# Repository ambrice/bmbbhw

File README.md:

# Big Mouth Billy Bass Master Control Program

This is the hardware design for the Big Mouth Billy Bass controller.  The current
software (zephyr version) runs on a group of 6 adafruit boards with a lot of
wires running between them.  So this is my first hardware design attempt, to use
the adafruit boards as a reference and compile them into one board.

The adafruit schematics are available under EAGLE which is a dead-end program, so
using KiCad 8 to design the board.  Started with brand-new KiCad 9, but it was
suggested that KiCad 8 would be more stable and have less potential issues with
manufacturing, Osh Park for example accepts KiCad 8 board files directly but not
KiCad 9 yet.

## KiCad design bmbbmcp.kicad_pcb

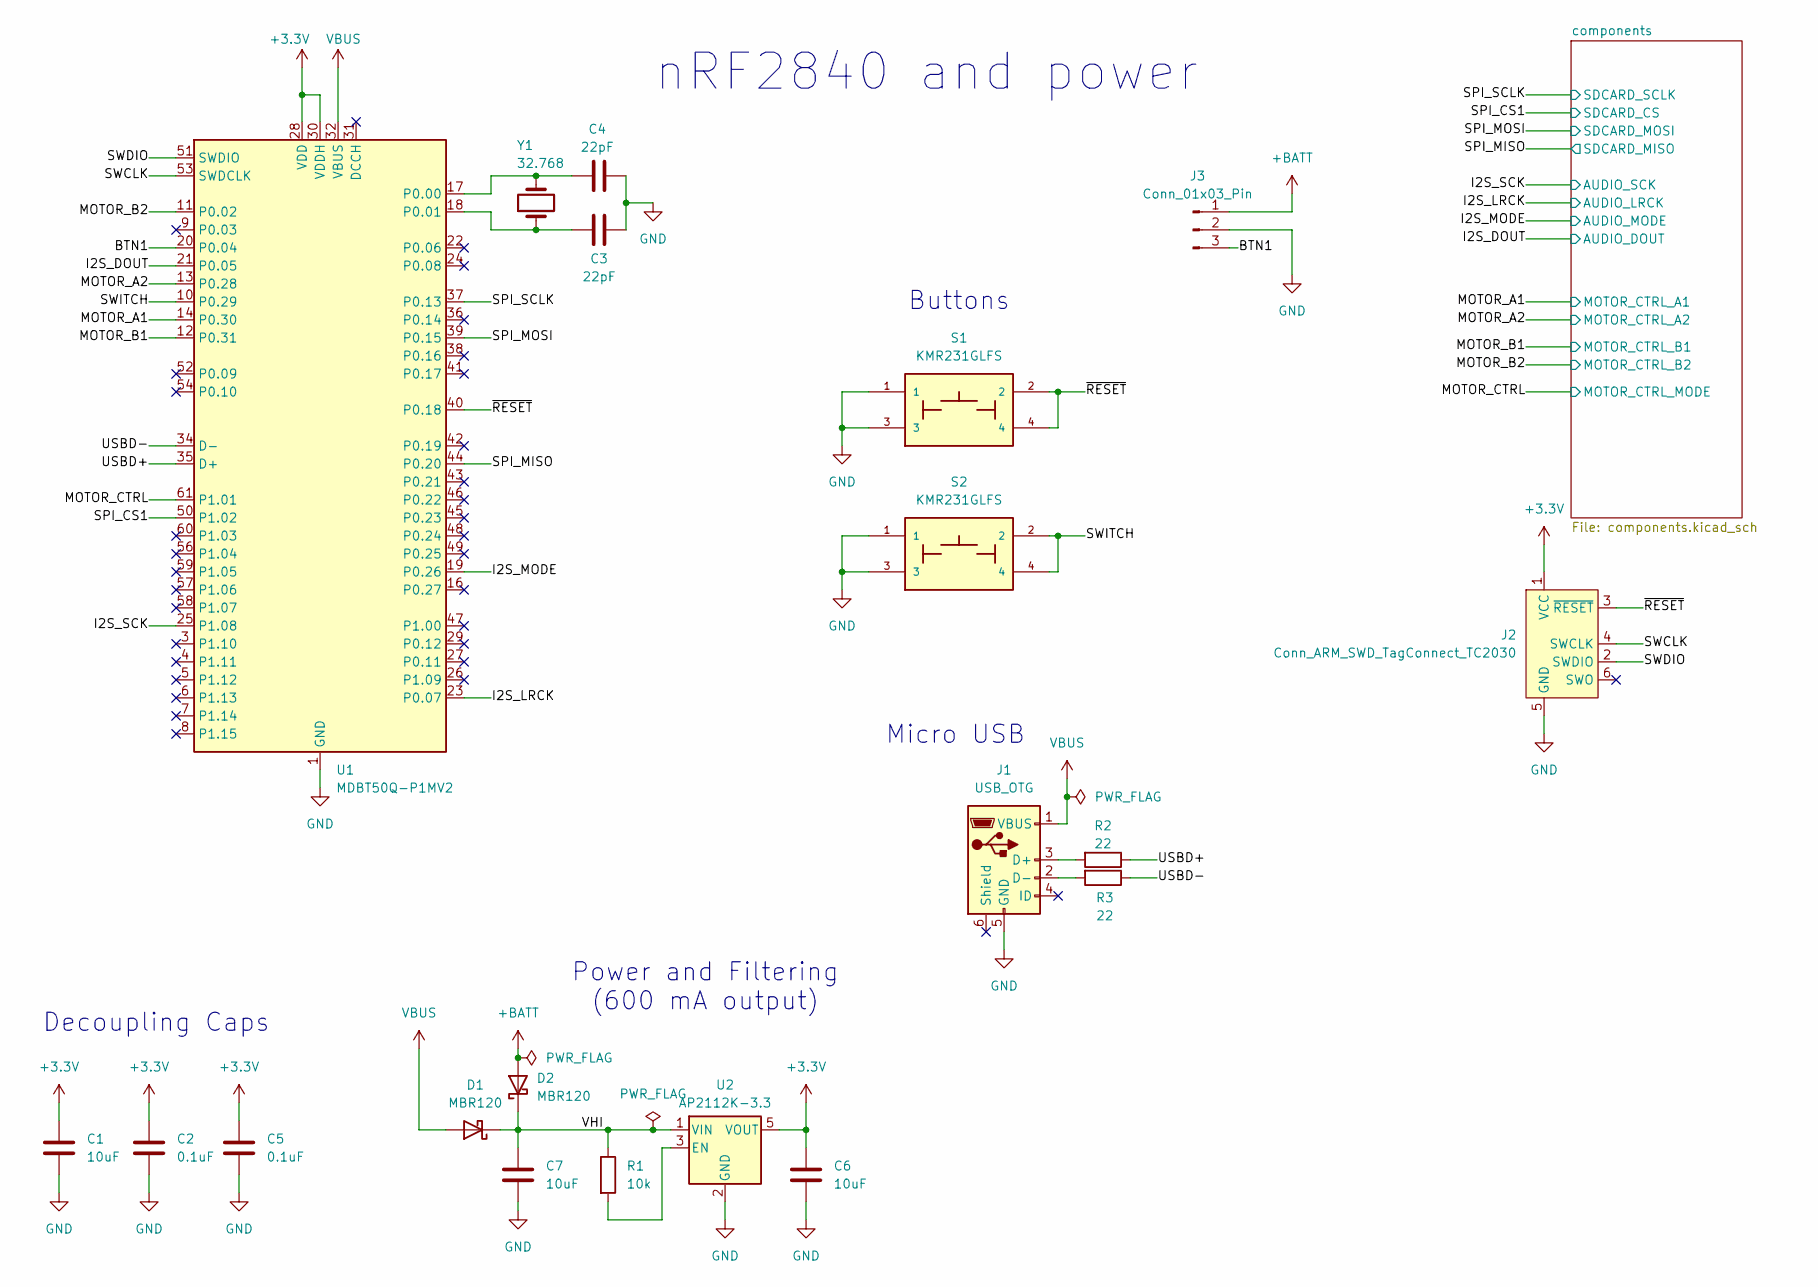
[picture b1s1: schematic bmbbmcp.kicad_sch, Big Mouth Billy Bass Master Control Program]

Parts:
C1, C6, C7: 10uF; C_0805_2012Metric; LCSC C15850
C2, C5: 0.1uF; C_0603_1608Metric; LCSC C14663
C3, C4: 22pF; C_0603_1608Metric; LCSC C1653
D1, D2: MBR120; D_SOD-123; LCSC C130880
J1: USB_OTG; USB_Micro-AB_Molex_47590-0001; LCSC C136001
J2: Conn_ARM_SWD_TagConnect_TC2030; Tag-Connect_TC2030-IDC-NL_2x03_P1.27mm_Vertical
J3: Conn_01x03_Pin; PinHeader_1x03_P2.54mm_Vertical
R1: 10k; R_0603_1608Metric; LCSC C25804
R2, R3: 22; R_0603_1608Metric; LCSC C23345
S1, S2: KMR231GLFS; SW4SMD_63X161LS; LCSC C99271
U1: MDBT50Q-P1MV2; Raytac_MDBT50Q; LCSC C5118826
U2: AP2112K-3.3; SOT-23-5; LCSC C51118
Y1: 32.768; Crystal_SMD_MicroCrystal_CC7V-T1A-2Pin_3.2x1.5mm; LCSC C620155

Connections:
+3.3V: C1.1, C2.1, C5.1, C6.1, J2.1 (VCC), U1.28 (VDD), U1.30 (VDDH), U2.5 (VOUT); also elsewhere on the board
+BATT: D2.2 (A), J3.1; also elsewhere on the board
/BTN1: J3.3, U1.20 (P0.04)
/I2S_DOUT: U1.21 (P0.05); also elsewhere on the board
/I2S_LRCK: U1.23 (P0.07); also elsewhere on the board
/I2S_MODE: U1.19 (P0.26); also elsewhere on the board
/I2S_SCK: U1.25 (P1.08); also elsewhere on the board
/MOTOR_A1: U1.14 (P0.30); also elsewhere on the board
/MOTOR_A2: U1.13 (P0.28); also elsewhere on the board
/MOTOR_B1: U1.12 (P0.31); also elsewhere on the board
/MOTOR_B2: U1.11 (P0.02); also elsewhere on the board
/MOTOR_CTRL: U1.61 (P1.01); also elsewhere on the board
/SPI_CS1: U1.50 (P1.02); also elsewhere on the board
/SPI_MISO: U1.44 (P0.20); also elsewhere on the board
/SPI_MOSI: U1.39 (P0.15); also elsewhere on the board
/SPI_SCLK: U1.37 (P0.13); also elsewhere on the board
/SWCLK: J2.4 (SWCLK), U1.53 (SWDCLK)
/SWDIO: J2.2 (SWDIO), U1.51 (SWDIO)
/SWITCH: S2.2, S2.4, U1.10 (P0.29)
/USBD+: R2.1, U1.35 (D+)
/USBD-: R3.1, U1.34 (D-)
/VHI: C7.1, D1.1 (K), D2.1 (K), R1.1, U2.1 (VIN)
/~RESET: J2.3 (~RESET), S1.2, S1.4, U1.40 (P0.18)
GND: C1.2, C2.2, C3.1, C4.1, C5.2, C6.2, C7.2, J1.5 (GND), J2.5 (GND), J3.2, S1.1, S1.3, S2.1, S2.3, U1.1 (GND), U1.2 (GND), U1.15 (GND), U1.33 (GND), U1.55 (GND), U2.2 (GND); also elsewhere on the board
unnamed: J1.3 (D+), R2.2
unnamed: J1.2 (D-), R3.2
unnamed: C4.2, U1.17 (P0.00), Y1.2
unnamed: C3.2, U1.18 (P0.01), Y1.1
unnamed: R1.2, U2.3 (EN)
VBUS: D1.2 (A), J1.1 (VBUS), U1.32 (VBUS)

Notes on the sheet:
Micro USB
Buttons
nRF2840 and power
Decoupling Caps
Power and Filtering (600 mA output)

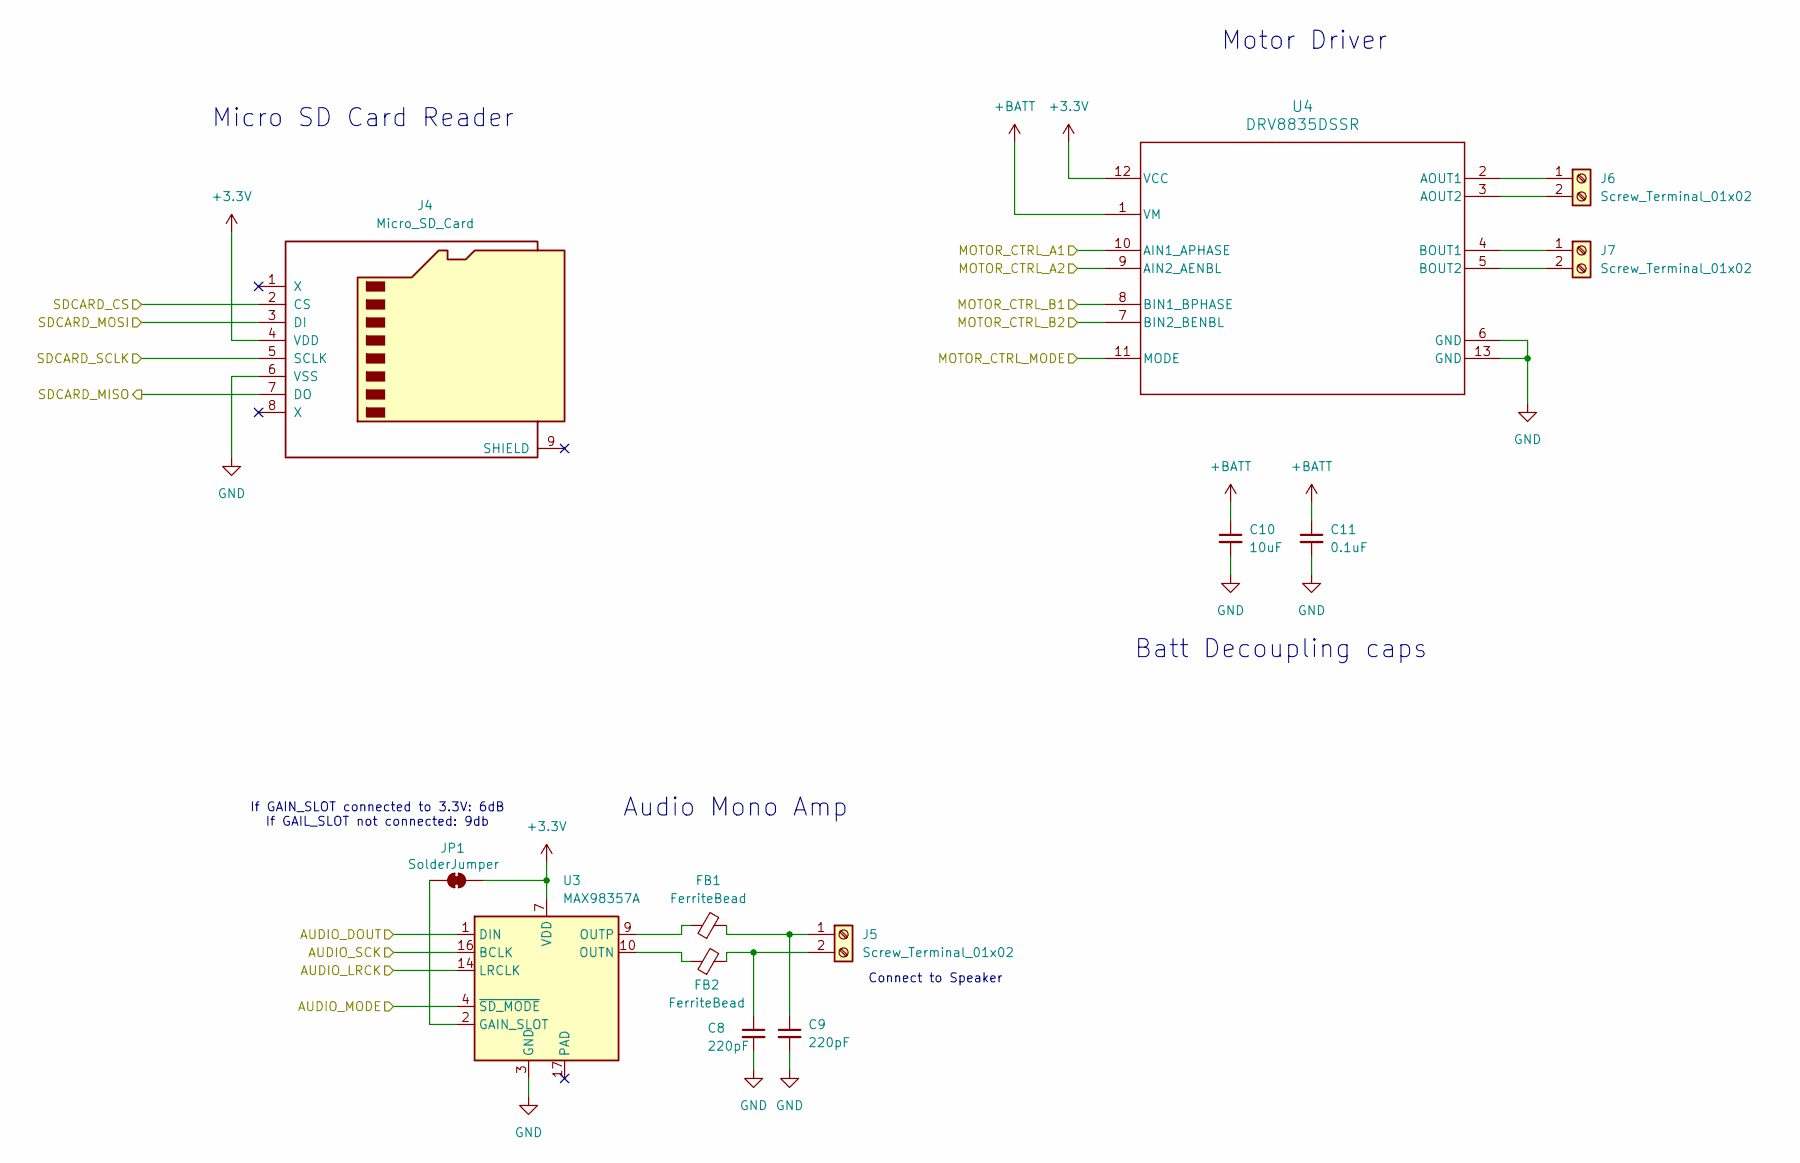
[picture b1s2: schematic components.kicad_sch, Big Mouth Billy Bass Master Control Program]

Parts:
C8, C9: 220pF; C_0805_2012Metric
C10: 10uF; C_0805_2012Metric
C11: 0.1uF; C_0603_1608Metric
FB1, FB2: FerriteBead; L_0805_2012Metric
J4: Micro_SD_Card; microSD_HC_Molex_104031-0811
J5, J6, J7: Screw_Terminal_01x02; TerminalBlock_MetzConnect_Type059_RT06302HBWC_1x02_P3.50mm_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
JP1: SolderJumper; SolderJumper-2_P1.3mm_Bridged_RoundedPad1.0x1.5mm
U3: MAX98357A; TQFN-16-1EP_3x3mm_P0.5mm_EP1.23x1.23mm
U4: DRV8835DSSR; DSS0012A

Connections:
+3.3V: J4.4 (VDD), JP1.2 (B), U3.7 (VDD), U3.8 (VDD), U4.12 (VCC); also elsewhere on the board
+BATT: C10.1, C11.1, U4.1 (VM); also elsewhere on the board
/I2S_DOUT: U3.1 (DIN); also elsewhere on the board
/I2S_LRCK: U3.14 (LRCLK); also elsewhere on the board
/I2S_MODE: U3.4 (~SD_MODE); also elsewhere on the board
/I2S_SCK: U3.16 (BCLK); also elsewhere on the board
/MOTOR_A1: U4.10 (AIN1_APHASE); also elsewhere on the board
/MOTOR_A2: U4.9 (AIN2_AENBL); also elsewhere on the board
/MOTOR_B1: U4.8 (BIN1_BPHASE); also elsewhere on the board
/MOTOR_B2: U4.7 (BIN2_BENBL); also elsewhere on the board
/MOTOR_CTRL: U4.11 (MODE); also elsewhere on the board
/SPI_CS1: J4.2 (CS); also elsewhere on the board
/SPI_MISO: J4.7 (DO); also elsewhere on the board
/SPI_MOSI: J4.3 (DI); also elsewhere on the board
/SPI_SCLK: J4.5 (SCLK); also elsewhere on the board
GND: C8.2, C9.2, C10.2, C11.2, J4.6 (VSS), U3.3 (GND), U3.11 (GND), U3.15 (GND), U4.6 (GND), U4.13 (GND), U4.V; also elsewhere on the board
unnamed: C9.1, FB1.2, J5.1
unnamed: C8.1, FB2.2, J5.2
unnamed: J6.1, U4.2 (AOUT1)
unnamed: J6.2, U4.3 (AOUT2)
unnamed: J7.1, U4.4 (BOUT1)
unnamed: J7.2, U4.5 (BOUT2)
unnamed: JP1.1 (A), U3.2 (GAIN_SLOT)
unnamed: FB2.1, U3.10 (OUTN)
unnamed: FB1.1, U3.9 (OUTP)

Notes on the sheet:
Connect to Speaker
Micro SD Card Reader
Audio Mono Amp
Motor Driver
Batt Decoupling caps
If GAIN_SLOT connected to 3.3V: 6dB If GAIL_SLOT not connected: 9db

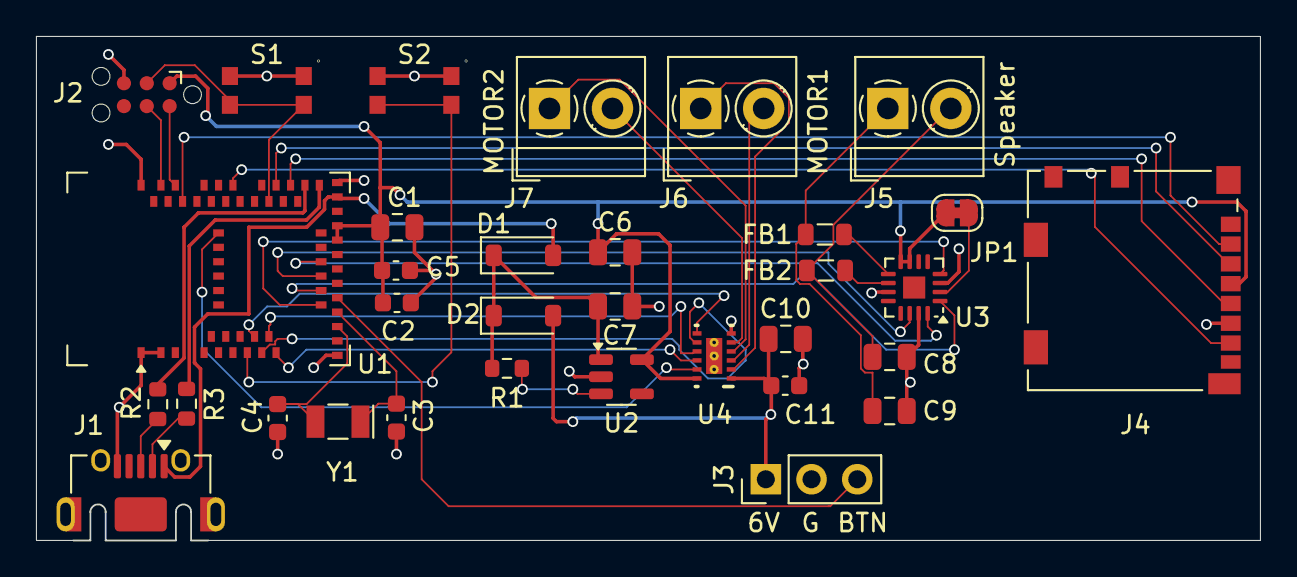
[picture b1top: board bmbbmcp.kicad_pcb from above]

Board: 4 copper layers, 68.0 x 28.0 mm, 33 parts (0 on the bottom side), 39 nets.

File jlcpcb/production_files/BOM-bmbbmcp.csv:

Comment,Designator,Footprint,LCSC,Quantity
220pF,"C8,C9",C_0805_2012Metric,C107145,2
DRV8835DSSR,U4,DSS0012A,C129328,1
MBR120,"D1,D2",D_SOD-123,C130880,2
USB_OTG,J1,USB_Micro-AB_Molex_47590-0001,C136001,1
0.1uF,"C11,C2,C5",C_0603_1608Metric,C14663,3
10uF,"C1,C10,C6,C7",C_0805_2012Metric,C15850,4
22pF,"C3,C4",C_0603_1608Metric,C1653,2
22,"R2,R3",R_0603_1608Metric,C23345,2
10k,R1,R_0603_1608Metric,C25804,1
FerriteBead,"FB1,FB2",L_0805_2012Metric,C442498,2
AP2112K-3.3,U2,SOT-23-5,C51118,1
MDBT50Q-P1MV2,U1,Raytac_MDBT50Q,C5119772,1
Micro_SD_Card,J4,microSD_HC_Molex_104031-0811,C585350,1
32.768,Y1,Crystal_SMD_MicroCrystal_CC7V-T1A-2Pin_3.2x1.5mm,C620155,1
MAX98357A,U3,TQFN-16-1EP_3x3mm_P0.5mm_EP1.23x1.23mm,C910544,1
KMR231GLFS,"S1,S2",SW4SMD_63X161LS,C99271,2

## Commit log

2025-03-14 Schematic updates
2025-03-14 Moving from KiCad 9.0 to 8.0.9
    KiCad 9 is very new and it was suggested that I should use stable KiCad 8 instead
2025-03-14 Adding README
2025-03-19 Updated with routing, passes almost all design rule checks
2025-03-20 Adding parts and gerber files from JLCPCB plugin
2025-03-26 Initial full board design
2025-04-21 Switch to three pin
2025-04-22 Switch MCU from MDBT50Q-1MV2 to MDBT50Q-P1MV2 (PCB antenna version, in stock)
